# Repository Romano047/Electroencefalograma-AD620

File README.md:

# Prótesis Electroencefalograma AD620
Electroencefalograma-AD620 Realizado en la Escuela de Educación Secundaria Técnica N°5 "2 de Abril" Temperley, Buenos Aires, Argentina. 

Proyecto objetivamente orientado a la investigación y el desarrollo con fines educativos de las señales emitidas por el cerebro e implementarlas en una prótesis de brazo.

Desarrollado por Iván Romano, 7mo 6ta, 2025.

Realizado en "Proyecto y Diseño Electrónico" a cargo del Prof. Martín Leguizamón. 

*PROYECTO ESCOLAR CONCLUIDO.*

Este repositorio será actualizado en caso de investigaciones futuras.

Diseño de Hardware Finalizado y presente en el repositorio. 

# Material y softare utilizados
- Desarrollo de PCB: KiCad 8.0 
- Simulador: MicroCap12
- Amplificadores : AD620an - LM358

# Guía de Repositorio
- Hardwre: Diseño de Módulos PCBs y huellas utilizadas en el proyecto.

  - Fuente_EEG
    - Fuente empleada en el proyecto adaptada al uso de ServoMotores como Output (DESCARTADO).

  - Amplificador_EEG
    - Ampificador Empleado en el proyecto.

  - MicroControlador_EEG: En desarrollo (Versión preeliminar en Alpha) DESCARTADO.

  - Trazado: En esta carpeta se encontrará el trazado empleado para la fabricación manual de las PCBs.

  - Simulación: Esquemático principal del proyecto simulado mediante el software de MicroCap.
 
  - Librerías externas empleadas:
    - E.E.S.T. n°5 , Prof. Mariano Bustos y alumnos del industrial de Temperley.
    - MacroLib , Prof. Maximiliano Andrés Barzola.
    - Logo R , huellas y logos creados por el director de este repositorio.

- 3D: Archivos correspondientes a los diseños 3D del proyecto (Soportes de PCBs).
- Informe: Informe detallado del proyecto, principios de funcionamiento, desarollo y conclusiones obtenidas, Archivo Diagrama de Gantt.
- Manual de Usuario.
- Funcionamiento: Fotos y videos de los resultados prácticos obtenidos. 

# Última Actualización

- Conclusión escolar del proyecto (20 de Nov de 2025).
- Informe final del proyecto.
- Manual de ususario.
- Resultados de funcionamiento.

Cámbios observables en rama "main".

v4.0 - 29 Noviembre 2025

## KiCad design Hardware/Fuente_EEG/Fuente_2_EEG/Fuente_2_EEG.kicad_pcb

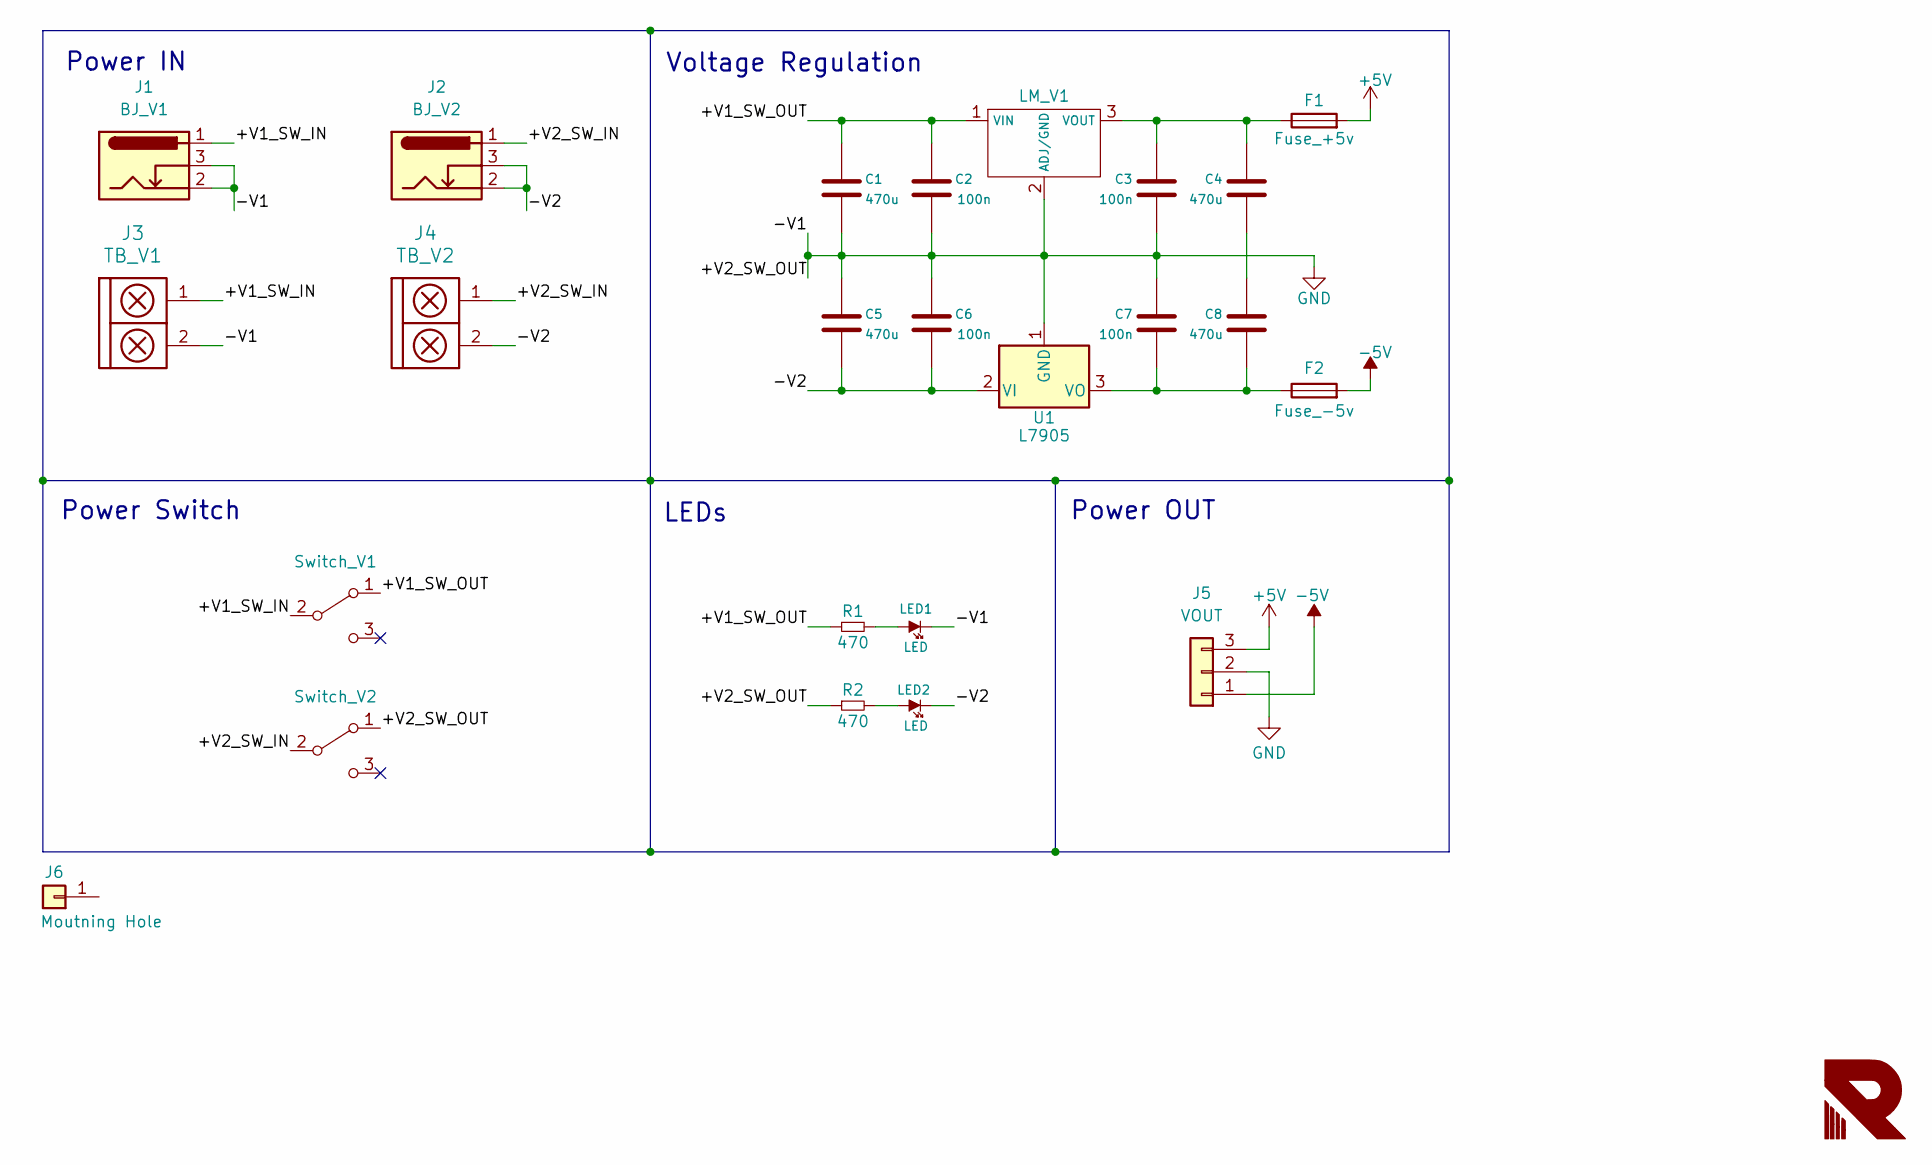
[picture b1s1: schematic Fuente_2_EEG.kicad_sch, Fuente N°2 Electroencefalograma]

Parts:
C1, C4, C5, C8: 470u; CAP_ELEC_8x11.5mm
C2, C3, C6, C7: 100n; C_0805
F1: Fuse_+5v; Fuse_Cylinder_8mm
F2: Fuse_-5v; Fuse_Cylinder_8mm
J1: BJ_V1; BarrelJack_Horizontal
J2: BJ_V2; BarrelJack_Horizontal
J3: TB_V1; BORNERA2_DUO
J4: TB_V2; BORNERA2_DUO
J5: VOUT; Molex_KK-254_AE-6410-03A_1x03_P2.54mm_Vertical
J6: Moutning Hole; hole_2mm
LED1, LED2: LED; led_3mm_green
LM_V1: TO-220
R1, R2: 470; R_0805
Switch_V1, Switch_V2: SW_SPDT; SW_SPDT_TH_Vertical
U1: L7905; TO-220

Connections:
+5V: F1.2, J5.3
-5V: F2.2, J5.1
/+V1_SW_IN: J1.1, J3.1, Switch_V1.2 (B)
/+V1_SW_OUT: C1.1, C2.1, LM_V1.1 (VIN), R1.1, Switch_V1.1 (A)
/+V2_SW_IN: J2.1, J4.1, Switch_V2.2 (B)
/-V2: C5.2, C6.2, J2.2, J2.3, J4.2, LED2.2 (K), U1.2 (VI)
GND: C1.2, C2.2, C3.2, C5.1, C6.1, C7.1, J1.2, J1.3, J3.2, J5.2, LED1.2 (K), LM_V1.2 (ADJ/GND), R2.1, Switch_V2.1 (A), U1.1 (GND)
unnamed: C4.2, C8.1
unnamed: LED1.1 (A), R1.2
unnamed: LED2.1 (A), R2.2
unnamed: C3.1, C4.1, F1.1, LM_V1.3 (VOUT)
unnamed: C7.2, C8.2, F2.1, U1.3 (VO)

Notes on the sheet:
Power OUT
LEDs
Power IN
Power Switch
Voltage Regulation

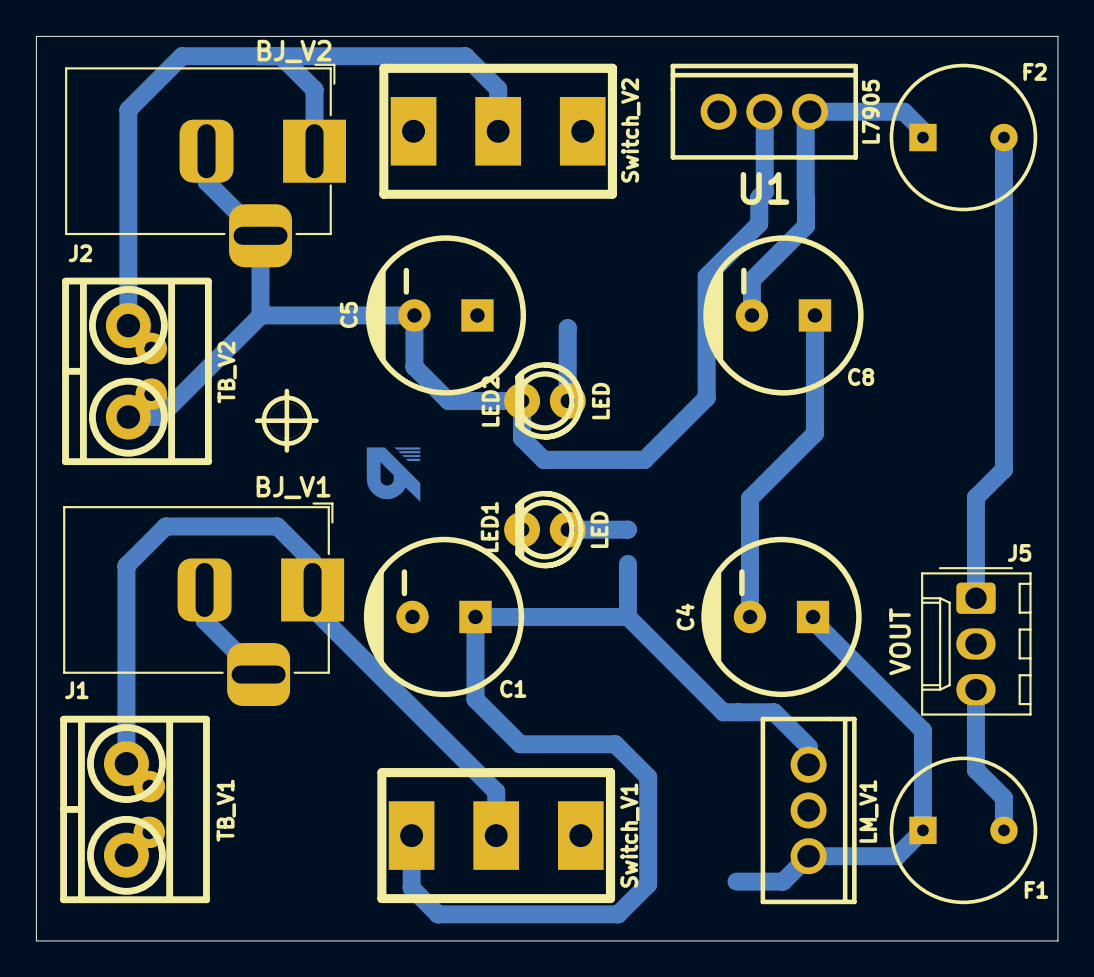
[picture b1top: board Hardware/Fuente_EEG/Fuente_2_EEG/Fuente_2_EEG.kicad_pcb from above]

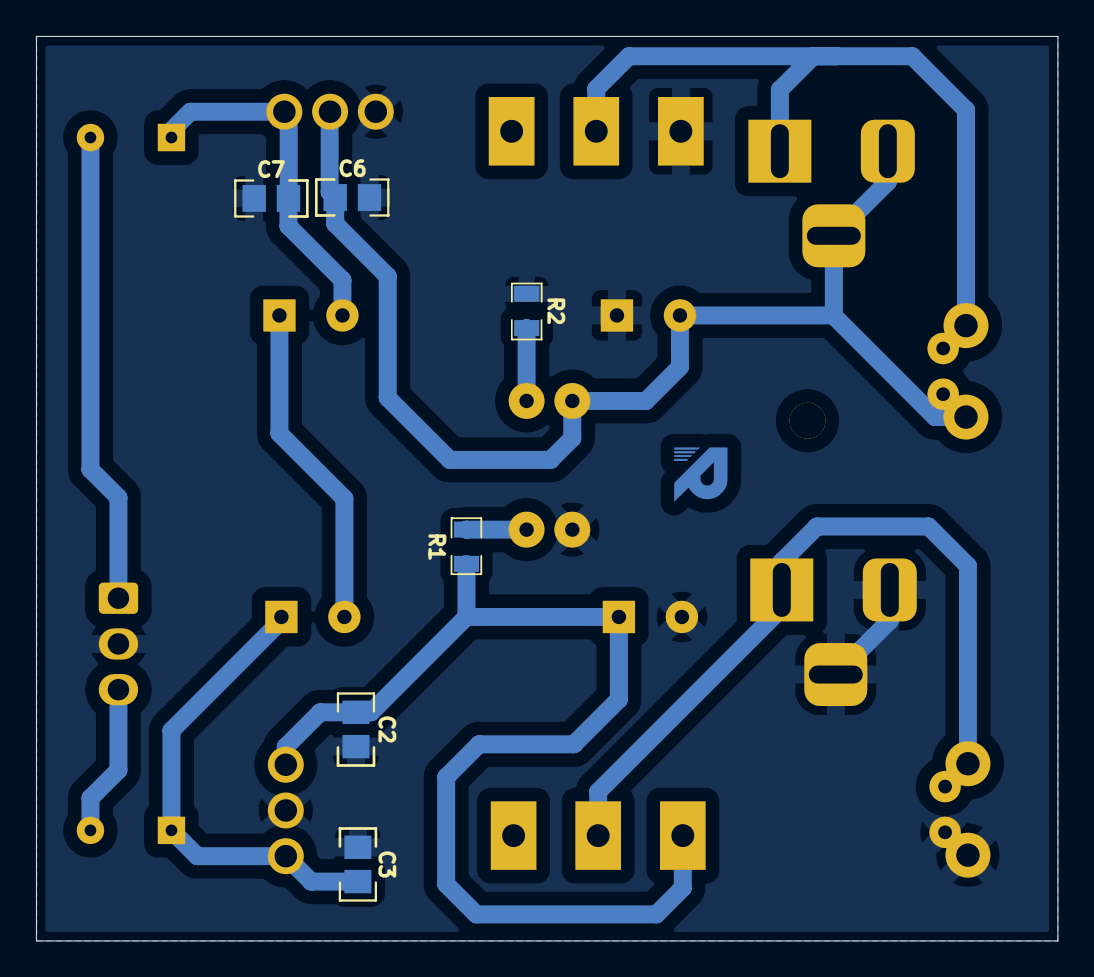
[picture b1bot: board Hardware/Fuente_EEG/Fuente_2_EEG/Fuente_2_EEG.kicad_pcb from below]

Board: 2 copper layers, 56.8 x 50.2 mm, 24 parts (6 on the bottom side), 12 nets.

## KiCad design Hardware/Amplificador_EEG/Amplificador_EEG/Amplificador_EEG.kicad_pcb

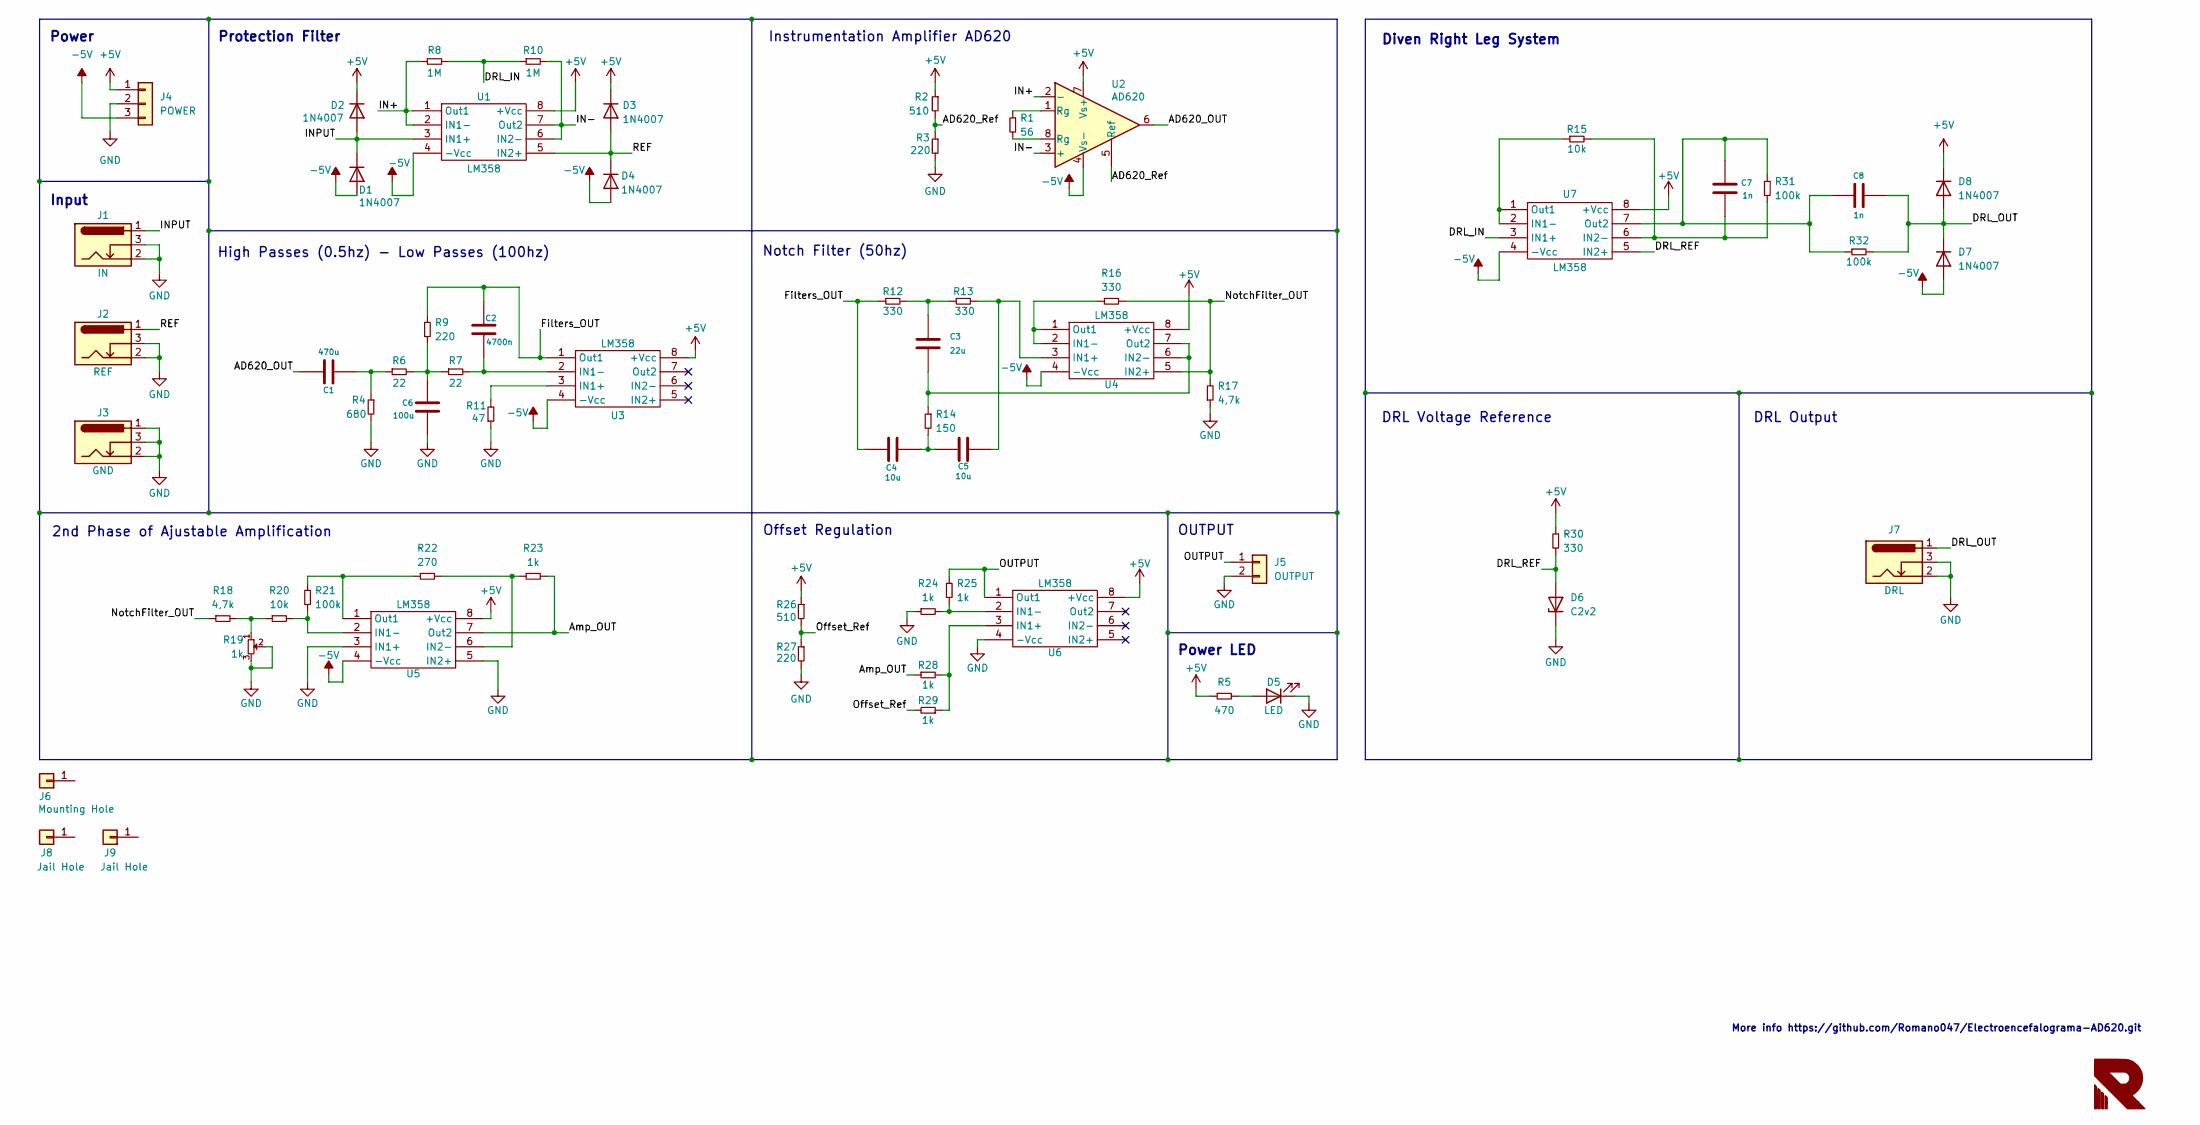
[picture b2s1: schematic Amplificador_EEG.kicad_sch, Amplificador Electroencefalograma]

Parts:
C1: 470u; CAP_ELEC_8x11.5mm
C2: 4700n; CAP_ELEC_5x11mm
C3: 22u; CAP_ELEC_5x11mm
C4, C5: 10u; CAP_ELEC_5x11mm
C6: 100u; C_0805
C7, C8: 1n; C_0805
D1, D2, D3, D4, D7, D8: 1N4007; DO-41
D5: LED; Led_0805
D6: C2v2; DO-41
J1: IN; BarrelJack_Horizontal
J2: REF; BarrelJack_Horizontal
J3: GND; BarrelJack_Horizontal
J4: POWER; Molex_KK-254_AE-6410-03A_1x03_P2.54mm_Vertical
J5: OUTPUT; Molex_KK-254_AE-6410-02A_1x02_P2.54mm_Vertical
J6: Mounting Hole; hole_2mm
J7: DRL; BarrelJack_Horizontal
J8, J9: Jail Hole; hole_2mm
R1: 56; R_0805
R2, R26: 510; RES0.3
R3, R9, R27: 220; R_0805
R4: 680; R_0805
R5: 470; R_0805
R6, R7: 22; R_0805
R8, R10: 1M; RES0.3
R11: 47; R_0805
R12, R13, R16, R30: 330; R_0805
R14: 150; R_0805
R15, R20: 10k; R_0805
R17, R18: 4,7k; R_0805
R19: 1k; Potenciometer_Trimpot
R21, R31, R32: 100k; R_0805
R22: 270; R_0805
R23, R24, R25, R28, R29: 1k; R_0805
U1, U3, U4, U5, U6, U7: LM358; SSOP-8
U2: AD620; DIP-8

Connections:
+5V: D2.1 (K), D3.1 (K), D8.1 (K), J4.1, R2.1, R5.1, R26.1, R30.1, U1.8 (+Vcc), U2.7 (Vs+), U3.8 (+Vcc), U4.8 (+Vcc), U5.8 (+Vcc), U6.8 (+Vcc), U7.8 (+Vcc)
-5V: D1.2 (A), D4.2 (A), D7.2 (A), J4.3, U1.4 (-Vcc), U2.4 (Vs-), U3.4 (-Vcc), U4.4 (-Vcc), U5.4 (-Vcc), U7.4 (-Vcc)
/AD620_OUT: C1.2, U2.6
/AD620_Ref: R2.2, R3.1, U2.5 (Ref)
/Amp_OUT: R23.2, R28.1, U5.7 (Out2)
/DRL_IN: R8.2, R10.1, U7.3 (IN1+)
/DRL_OUT: C8.2, D7.1 (K), D8.2 (A), J7.1, R32.2
/DRL_REF: D6.2 (A), R30.2, U7.5 (IN2+)
/Filters_OUT: C2.1, C4.1, R9.2, R12.1, U3.1 (Out1)
/IN+: R8.1, U1.1 (Out1), U1.2 (IN1-), U2.2 (-)
/IN-: R10.2, U1.6 (IN2-), U1.7 (Out2), U2.3 (+)
/INPUT: D1.1 (K), D2.2 (A), J1.1, U1.3 (IN1+)
/NotchFilter_OUT: R16.2, R17.2, R18.1, U4.5 (IN2+)
/OUTPUT: J5.1, R25.2, U6.1 (Out1)
/Offset_Ref: R26.2, R27.1, R29.2
/REF: D3.2 (A), D4.1 (K), J2.1, U1.5 (IN2+)
GND: C6.2, D5.1 (K), D6.1 (K), J1.2, J1.3, J2.2, J2.3, J3.1, J3.2, J3.3, J4.2, J5.2, J7.2, J7.3, R3.2, R4.2, R11.1, R17.1, R19.2, R19.3, R24.1, R27.2, U5.3 (IN1+), U5.5 (IN2+), U6.4 (-Vcc)
unnamed: C1.1, R4.1, R6.1
unnamed: C3.1, R12.2, R13.1
unnamed: C4.2, C5.1, R14.2
unnamed: C6.1, R6.2, R7.1, R9.1
unnamed: D5.2 (A), R5.2
unnamed: R1.1, U2.1 (Rg)
unnamed: R1.2, U2.8 (Rg)
unnamed: R18.2, R19.1, R20.1
unnamed: R11.2, U3.3 (IN1+)
unnamed: C2.2, R7.2, U3.2 (IN1-)
unnamed: C5.2, R13.2, U4.3 (IN1+)
unnamed: R16.1, U4.1 (Out1), U4.2 (IN1-)
unnamed: C3.2, R14.1, U4.6 (IN2-), U4.7 (Out2)
unnamed: R20.2, R21.2, U5.2 (IN1-)
unnamed: R22.2, R23.1, U5.6 (IN2-)
unnamed: R21.1, R22.1, U5.1 (Out1)
unnamed: R28.2, R29.1, U6.3 (IN1+)
unnamed: R24.2, R25.1, U6.2 (IN1-)
unnamed: R15.1, U7.1 (Out1), U7.2 (IN1-)
unnamed: C7.2, R15.2, R31.2, U7.6 (IN2-)
unnamed: C7.1, C8.1, R31.1, R32.1, U7.7 (Out2)

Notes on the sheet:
More info https://github.com/Romano047/Electroencefalograma-AD620.git
Offset Regulation
OUTPUT
2nd Phase of Ajustable Amplification
Power LED
High Passes (0.5hz) - Low Passes (100hz)
Instrumentation Amplifier AD620
Diven Right Leg System
Protection Filter
Power
Notch Filter (50hz)
Input
DRL Output
DRL Voltage Reference

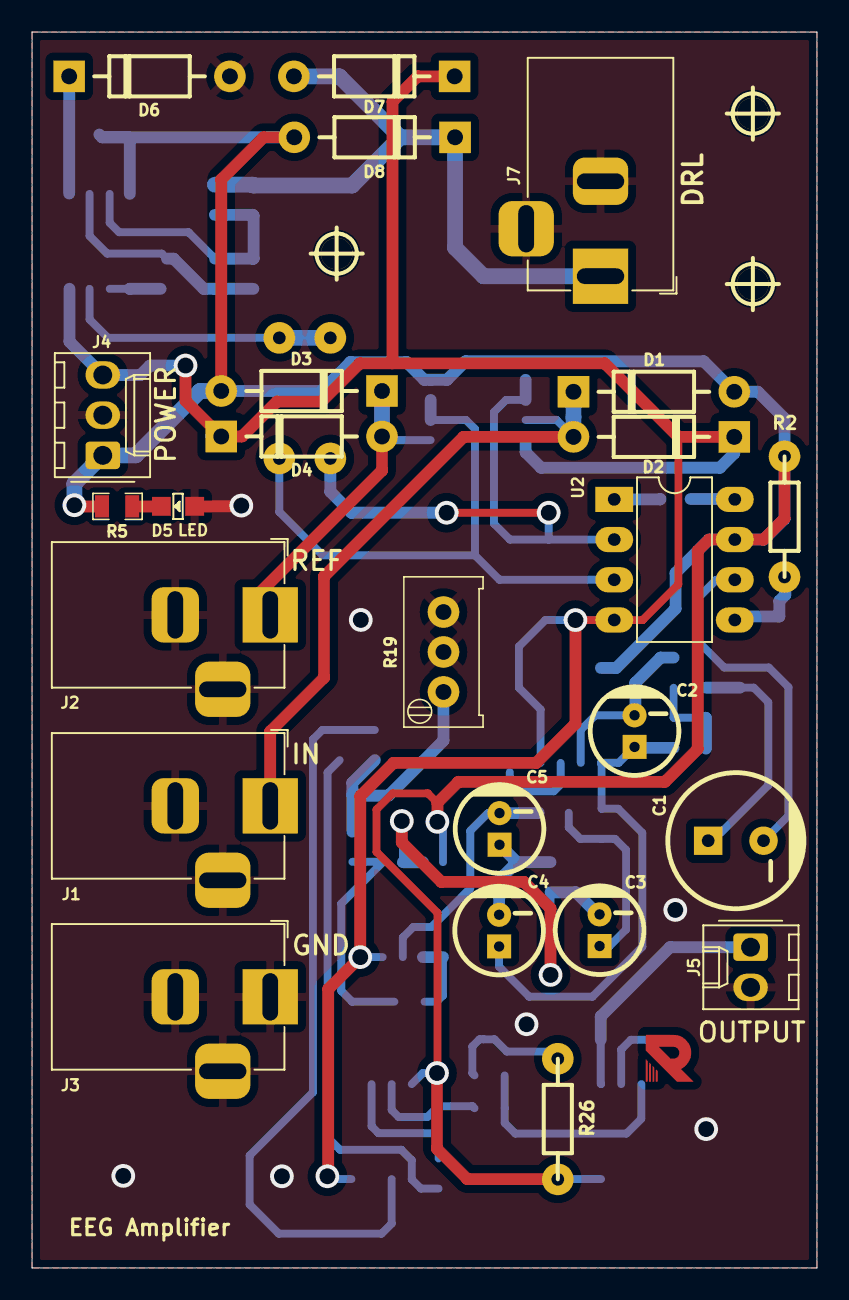
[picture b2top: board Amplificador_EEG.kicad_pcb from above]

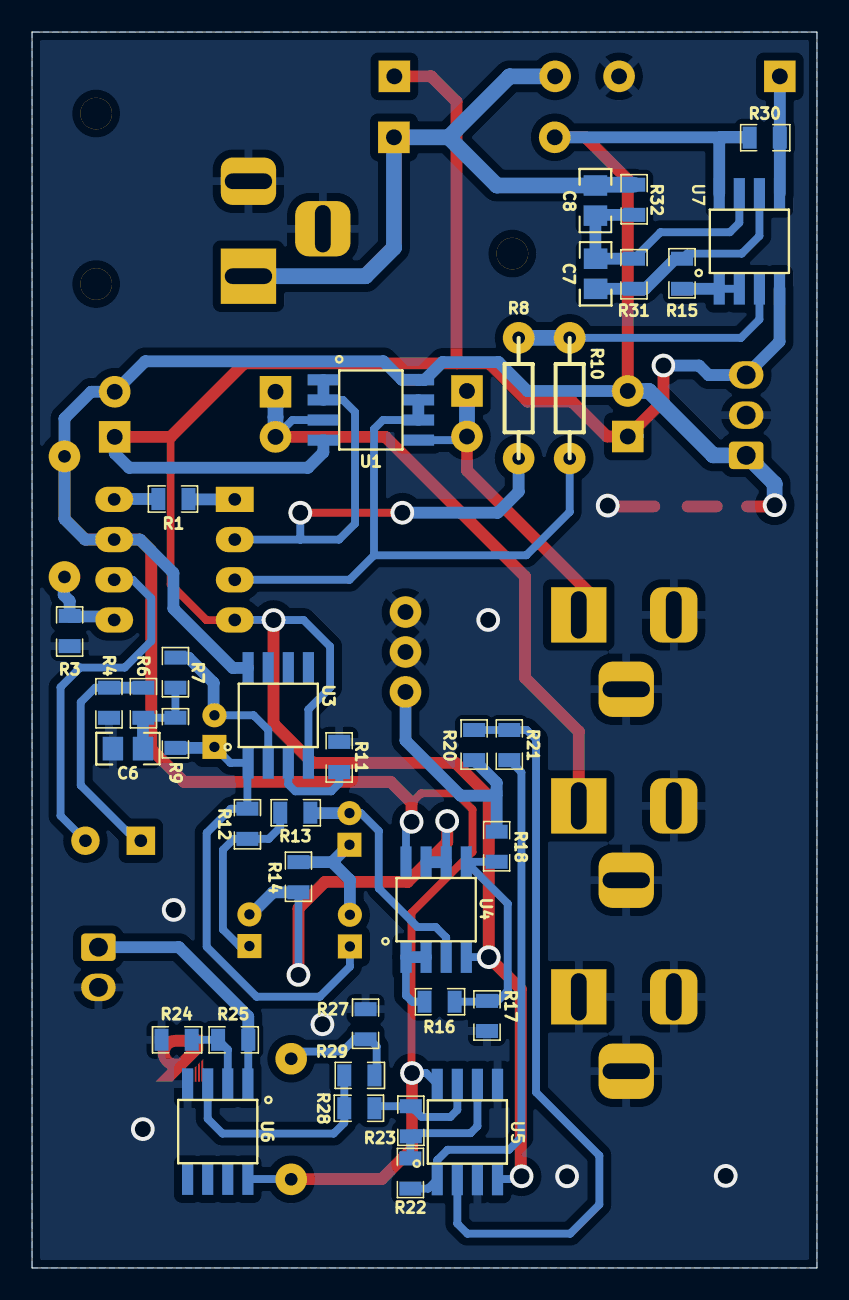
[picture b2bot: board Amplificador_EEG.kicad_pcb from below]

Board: 2 copper layers, 49.6 x 78.1 mm, 64 parts (37 on the bottom side), 38 nets.

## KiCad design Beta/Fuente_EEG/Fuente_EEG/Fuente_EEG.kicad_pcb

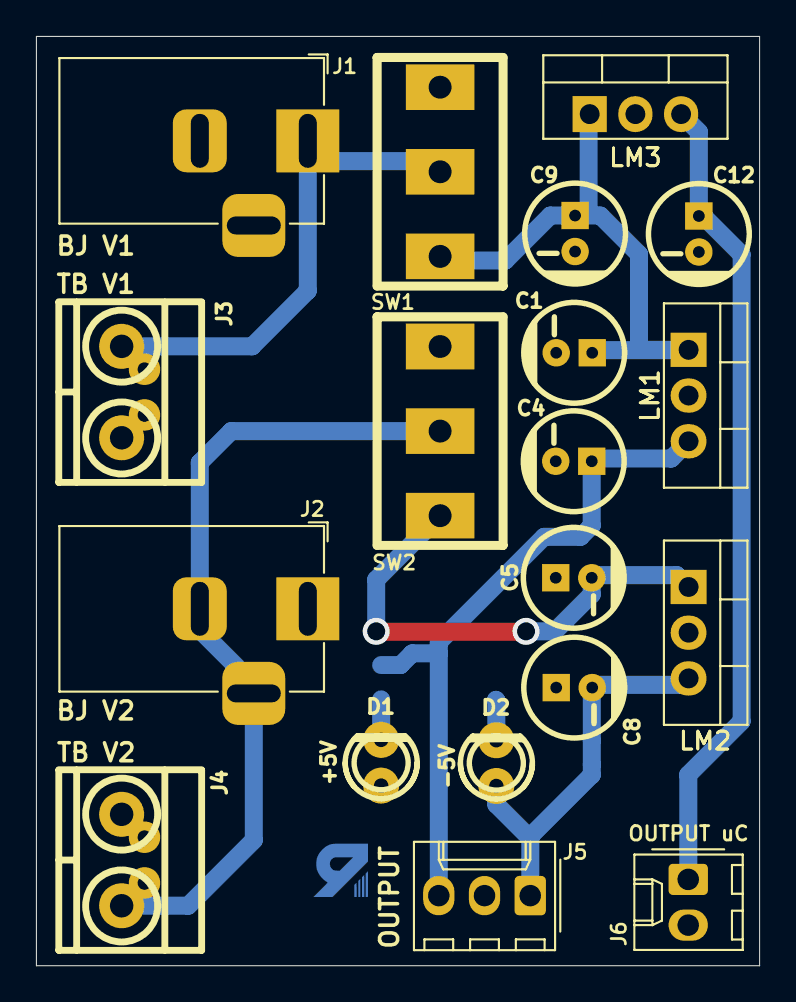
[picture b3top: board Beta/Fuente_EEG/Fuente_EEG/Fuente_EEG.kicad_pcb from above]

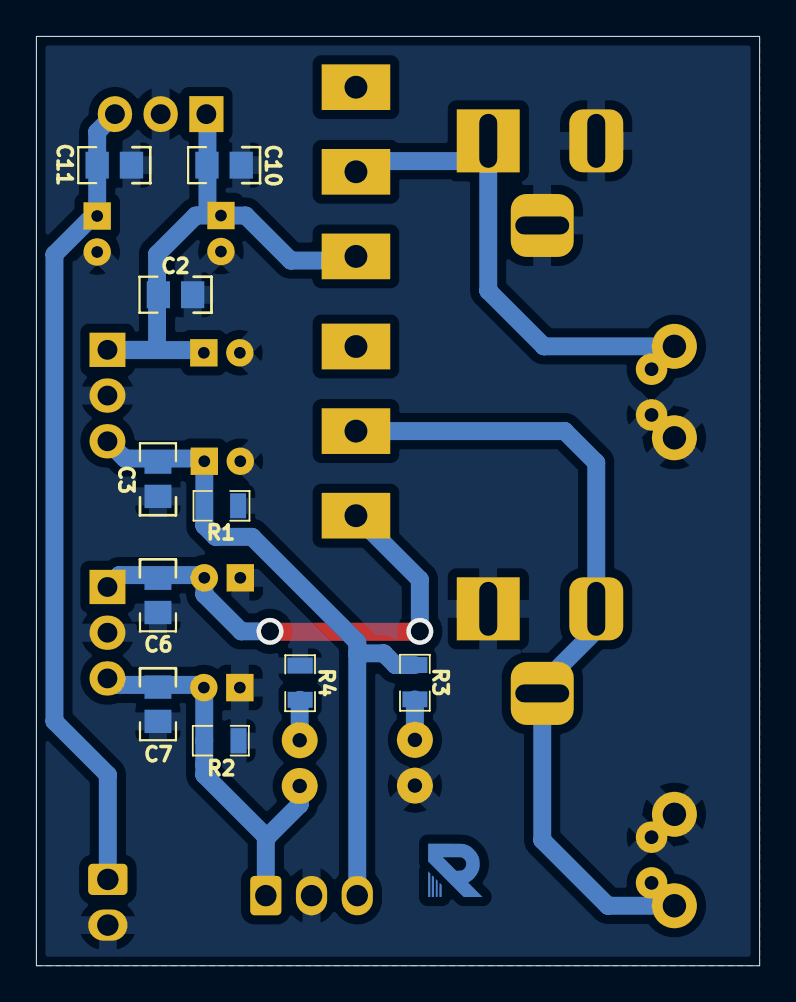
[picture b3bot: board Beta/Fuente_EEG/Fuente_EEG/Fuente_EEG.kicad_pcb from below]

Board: 2 copper layers, 40.2 x 51.6 mm, 29 parts (10 on the bottom side), 10 nets.

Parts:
C1, C5, C9: 470u; CAP_ELEC_5x11mm
C2, C3, C6, C7, C10, C11: 100n; C_0805
C4, C8, C12: 100u; CAP_ELEC_5x11mm
D1: +5V; led_3mm_green
D2: -5V; led_3mm_red
J1: BJ V1; BarrelJack_Horizontal
J2: BJ V2; BarrelJack_Horizontal
J3: TB V1; BORNERA2_DUO
J4: TB V2; BORNERA2_DUO
J5: OUTPUT; Molex_KK-254_AE-6410-03A_1x03_P2.54mm_Vertical
J6: OUTPUT uC; Molex_KK-254_AE-6410-02A_1x02_P2.54mm_Vertical
LM1, LM2, LM3: LM7805; TO-220-3_Vertical
R1, R2: 100; R_0805
R3, R4: 470; R_0805
SW1, SW2: SW_SPDT; SW_SPDT_TH_Vertical

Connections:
+5V: C3.1, C4.1, J5.3, LM1.3 (VOUT), R1.1, R3.1
-5V: C7.2, C8.2, D2.1 (K), J5.1, LM2.3 (VOUT), R2.2
/-V2: J2.2, J2.3, J4.2, SW2.2 (B)
/POWER_uC: C11.1, C12.1, J6.1, LM3.3 (VOUT)
/V1: J1.1, J3.1, SW1.2 (B)
/Vcc1: C1.1, C2.1, C9.1, C10.1, LM1.1 (VIN), LM3.1 (VIN), SW1.1 (A)
/Vcc2: C5.2, C6.2, LM2.1 (VIN), SW2.1 (A)
GND: C1.2, C2.2, C3.2, C4.2, C5.1, C6.1, C7.1, C8.1, C9.2, C10.2, C11.2, C12.2, D1.1 (K), J1.2, J1.3, J2.1, J3.2, J4.1, J5.2, J6.2, LM1.2 (ADJ/GND), LM2.2 (ADJ/GND), LM3.2 (ADJ/GND), R1.2, R2.1, R4.1
unnamed: D1.2 (A), R3.2
unnamed: D2.2 (A), R4.2

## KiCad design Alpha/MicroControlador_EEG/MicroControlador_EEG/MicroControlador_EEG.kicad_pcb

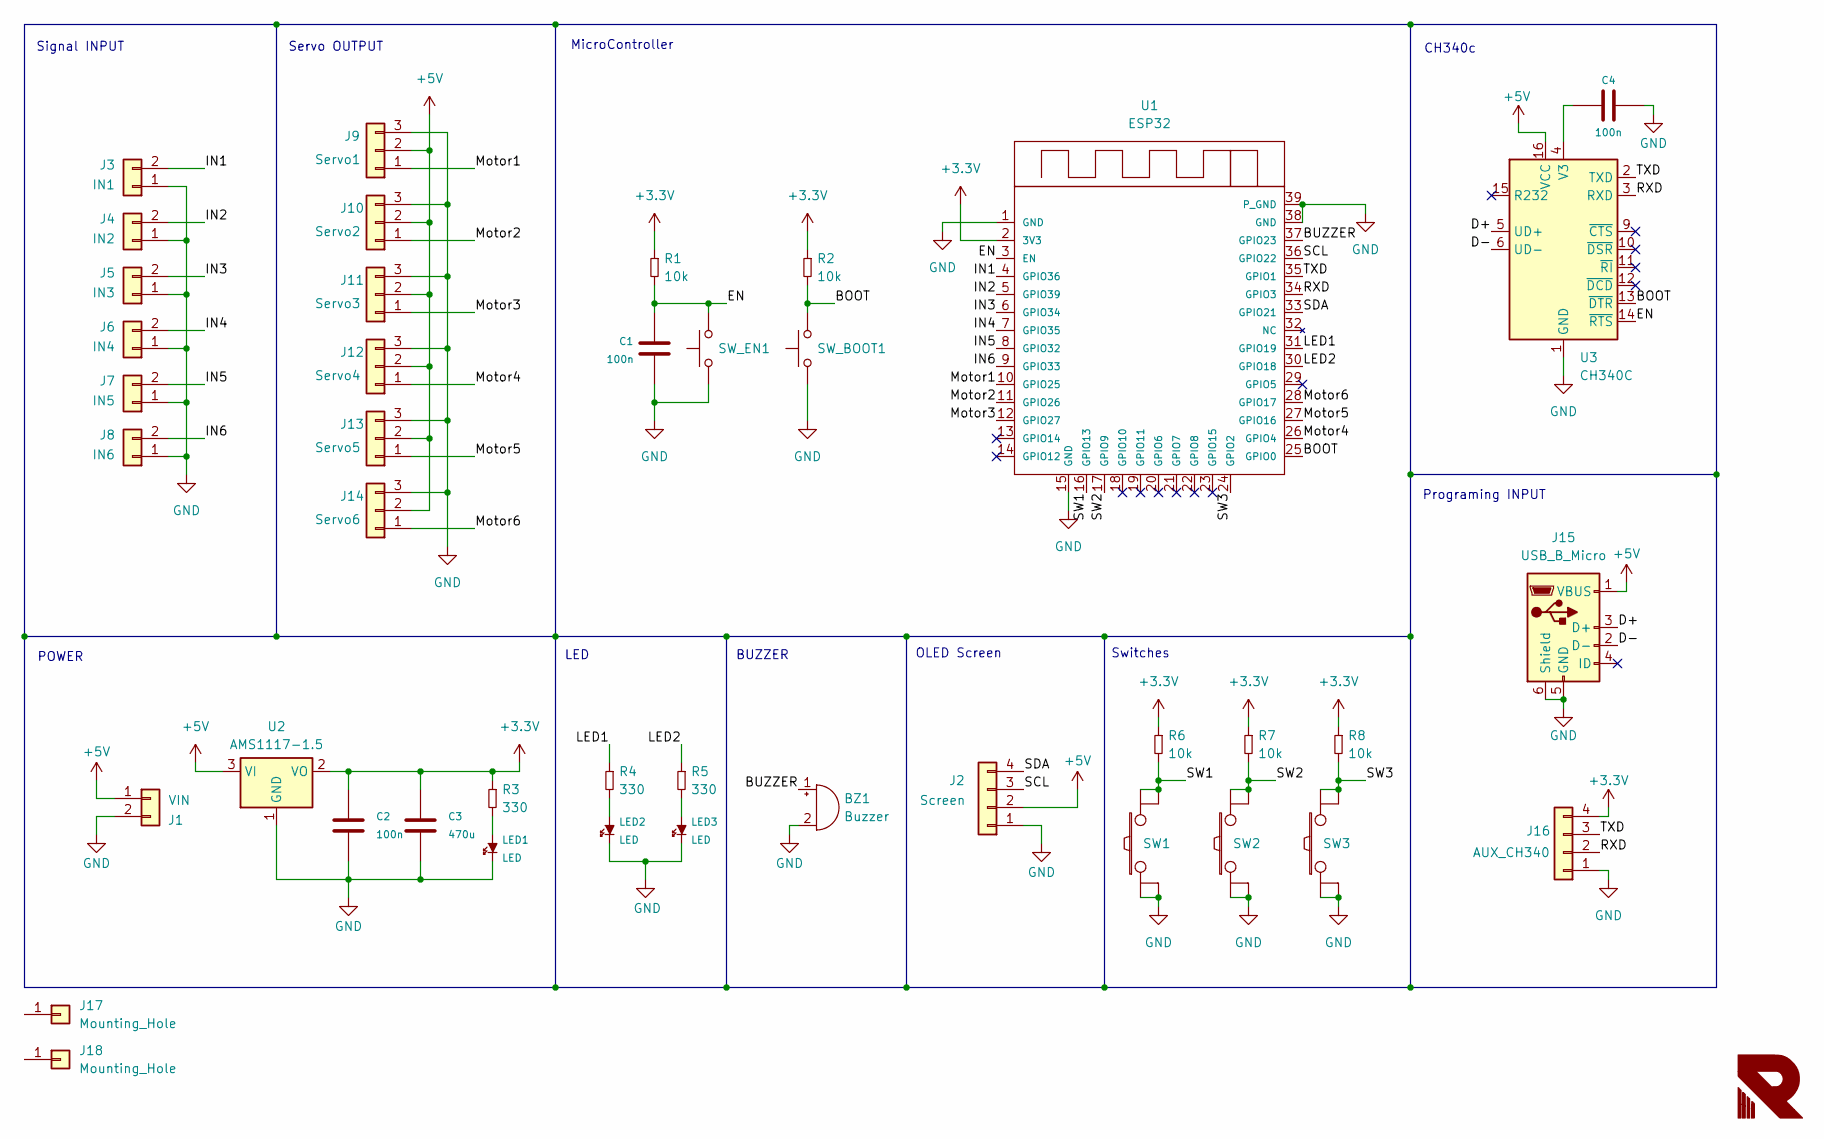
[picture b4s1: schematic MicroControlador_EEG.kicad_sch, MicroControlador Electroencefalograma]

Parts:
BZ1: Buzzer; Buzzer_12mm
C1, C2, C4: 100n; C_0805
C3: 470u; CAP_ELEC_8x11.5mm
J1: VIN; Molex_KK-254_AE-6410-02A_1x02_P2.54mm_Vertical
J2: Screen; Molex_KK-254_AE-6410-04A_1x04_P2.54mm_Vertical
J3: IN1; Molex_KK-254_AE-6410-02A_1x02_P2.54mm_Vertical
J4: IN2; Molex_KK-254_AE-6410-02A_1x02_P2.54mm_Vertical
J5: IN3; Molex_KK-254_AE-6410-02A_1x02_P2.54mm_Vertical
J6: IN4; Molex_KK-254_AE-6410-02A_1x02_P2.54mm_Vertical
J7: IN5; Molex_KK-254_AE-6410-02A_1x02_P2.54mm_Vertical
J8: IN6; Molex_KK-254_AE-6410-02A_1x02_P2.54mm_Vertical
J9: Servo1; Molex_KK-254_AE-6410-03A_1x03_P2.54mm_Vertical
J10: Servo2; Molex_KK-254_AE-6410-03A_1x03_P2.54mm_Vertical
J11: Servo3; Molex_KK-254_AE-6410-03A_1x03_P2.54mm_Vertical
J12: Servo4; Molex_KK-254_AE-6410-03A_1x03_P2.54mm_Vertical
J13: Servo5; Molex_KK-254_AE-6410-03A_1x03_P2.54mm_Vertical
J14: Servo6; Molex_KK-254_AE-6410-03A_1x03_P2.54mm_Vertical
J15: USB_B_Micro; USB_Micro-AB_Molex_47590-0001
J16: AUX_CH340; Molex_KK-254_AE-6410-04A_1x04_P2.54mm_Vertical
J17, J18: Mounting_Hole; hole_2mm
LED1, LED2, LED3: LED; LED_1206
R1, R2, R6, R7, R8: 10k; R_0805
R3, R4, R5: 330; R_0805
SW1, SW2, SW3: SW_PUSH; Pulsador_TH_4
SW_BOOT1: SW_Push; Pulsador_SMD_2_BAJO
SW_EN1: SW_Push; Pulsador_SMD_2_BAJO
U1: ESP32; ESP-WROOM-32
U2: AMS1117-1.5; SOT-223-3_TabPin2
U3: CH340C; SOIC-16_3.9x9.9mm_P1.27mm

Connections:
+3.3V: C2.1, C3.1, J16.4, R1.1, R2.1, R3.1, R6.1, R7.1, R8.1, U1.2 (3V3), U2.2 (VO)
+5V: J1.1, J2.2, J9.2, J10.2, J11.2, J12.2, J13.2, J14.2, J15.1 (VBUS), U2.3 (VI), U3.16 (VCC)
/BOOT: R2.2, SW_BOOT1.2, U1.25 (GPIO0), U3.13 (~DTR)
/BUZZER: BZ1.1 (-), U1.37 (GPIO23)
/D+: J15.3 (D+), U3.5 (UD+)
/D-: J15.2 (D-), U3.6 (UD-)
/EN: C1.1, R1.2, SW_EN1.2, U1.3 (EN), U3.14 (~RTS)
/IN1: J3.2, U1.4 (GPIO36)
/IN2: J4.2, U1.5 (GPIO39)
/IN3: J5.2, U1.6 (GPIO34)
/IN4: J6.2, U1.7 (GPIO35)
/IN5: J7.2, U1.8 (GPIO32)
/IN6: J8.2, U1.9 (GPIO33)
/LED1: R4.1, U1.31 (GPIO19)
/LED2: R5.1, U1.30 (GPIO18)
/Motor1: J9.1, U1.10 (GPIO25)
/Motor2: J10.1, U1.11 (GPIO26)
/Motor3: J11.1, U1.12 (GPIO27)
/Motor4: J12.1, U1.26 (GPIO4)
/Motor5: J13.1, U1.27 (GPIO16)
/Motor6: J14.1, U1.28 (GPIO17)
/RXD: J16.2, U1.34 (GPIO3), U3.3 (RXD)
/SCL: J2.3, U1.36 (GPIO22)
/SDA: J2.4, U1.33 (GPIO21)
/SW1: R6.2, SW1.3, SW1.4, U1.16 (GPIO13)
/SW2: R7.2, SW2.3, SW2.4, U1.17 (GPIO9)
/SW3: R8.2, SW3.3, SW3.4, U1.24 (GPIO2)
/TXD: J16.3, U1.35 (GPIO1), U3.2 (TXD)
GND: BZ1.2 (+), C1.2, C2.2, C3.2, C4.2, J1.2, J2.1, J3.1, J4.1, J5.1, J6.1, J7.1, J8.1, J9.3, J10.3, J11.3, J12.3, J13.3, J14.3, J15.5 (GND), J15.6 (Shield), J16.1, LED1.2 (K), LED2.2 (K), LED3.2 (K), SW1.1, SW1.2, SW2.1, SW2.2, SW3.1, SW3.2, SW_BOOT1.1, SW_EN1.1, U1.1 (GND), U1.15 (GND), U1.38 (GND), U1.39 (P_GND), U2.1 (GND), U3.1 (GND)
unnamed: LED1.1 (A), R3.2
unnamed: LED2.1 (A), R4.2
unnamed: LED3.1 (A), R5.2
unnamed: C4.1, U3.4 (V3)

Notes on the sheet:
Programing INPUT
CH340c
BUZZER
POWER
Switches
OLED Screen
Signal INPUT
MicroController
Servo OUTPUT
LED

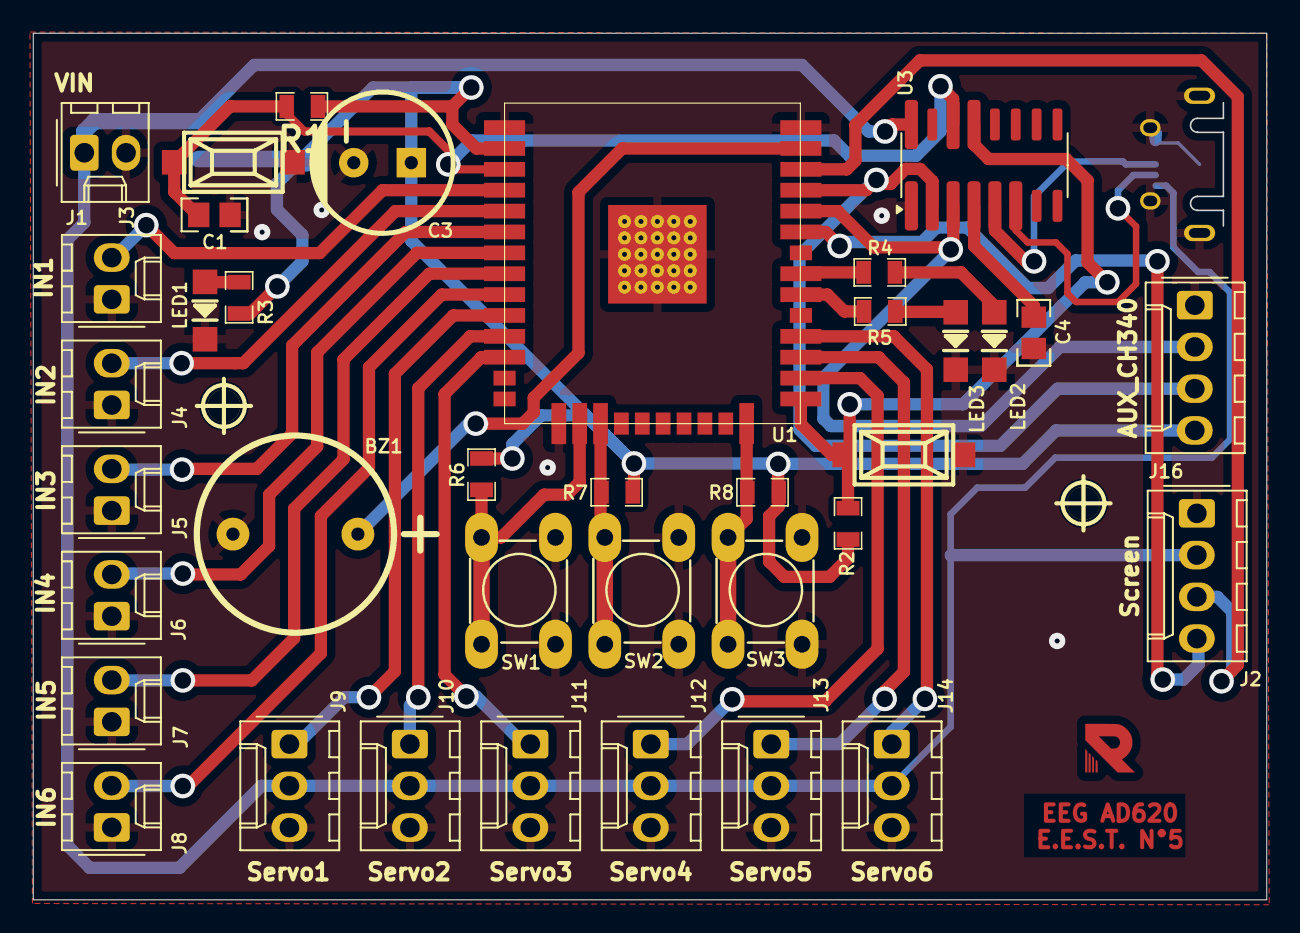
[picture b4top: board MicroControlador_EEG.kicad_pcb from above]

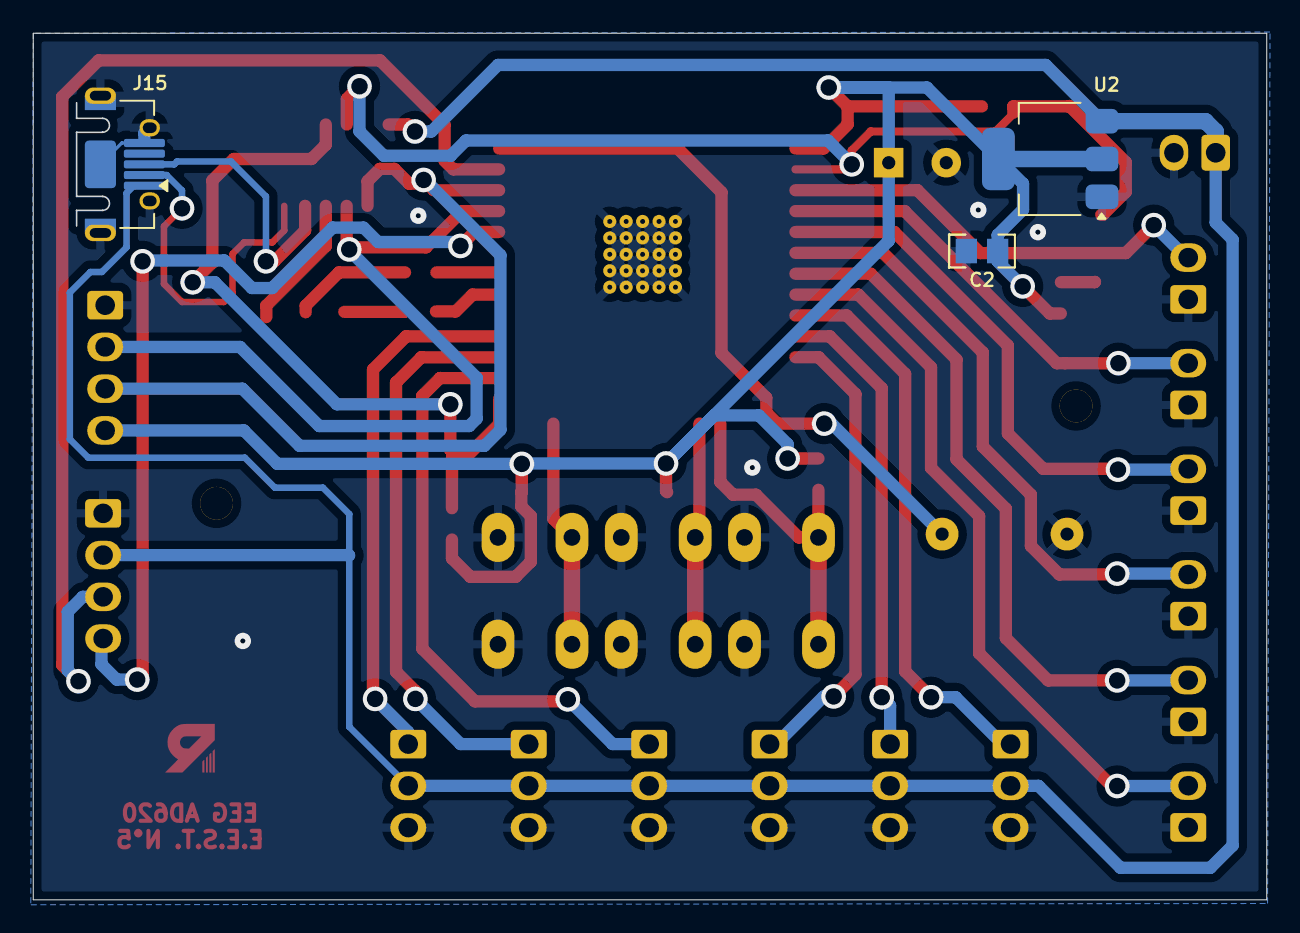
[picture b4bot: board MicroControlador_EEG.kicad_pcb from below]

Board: 2 copper layers, 75.0 x 52.7 mm, 42 parts (3 on the bottom side), 33 nets.
